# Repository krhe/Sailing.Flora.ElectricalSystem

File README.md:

# Sailing.Flora.ElectricalSystem
Electrical Diagram for Flora

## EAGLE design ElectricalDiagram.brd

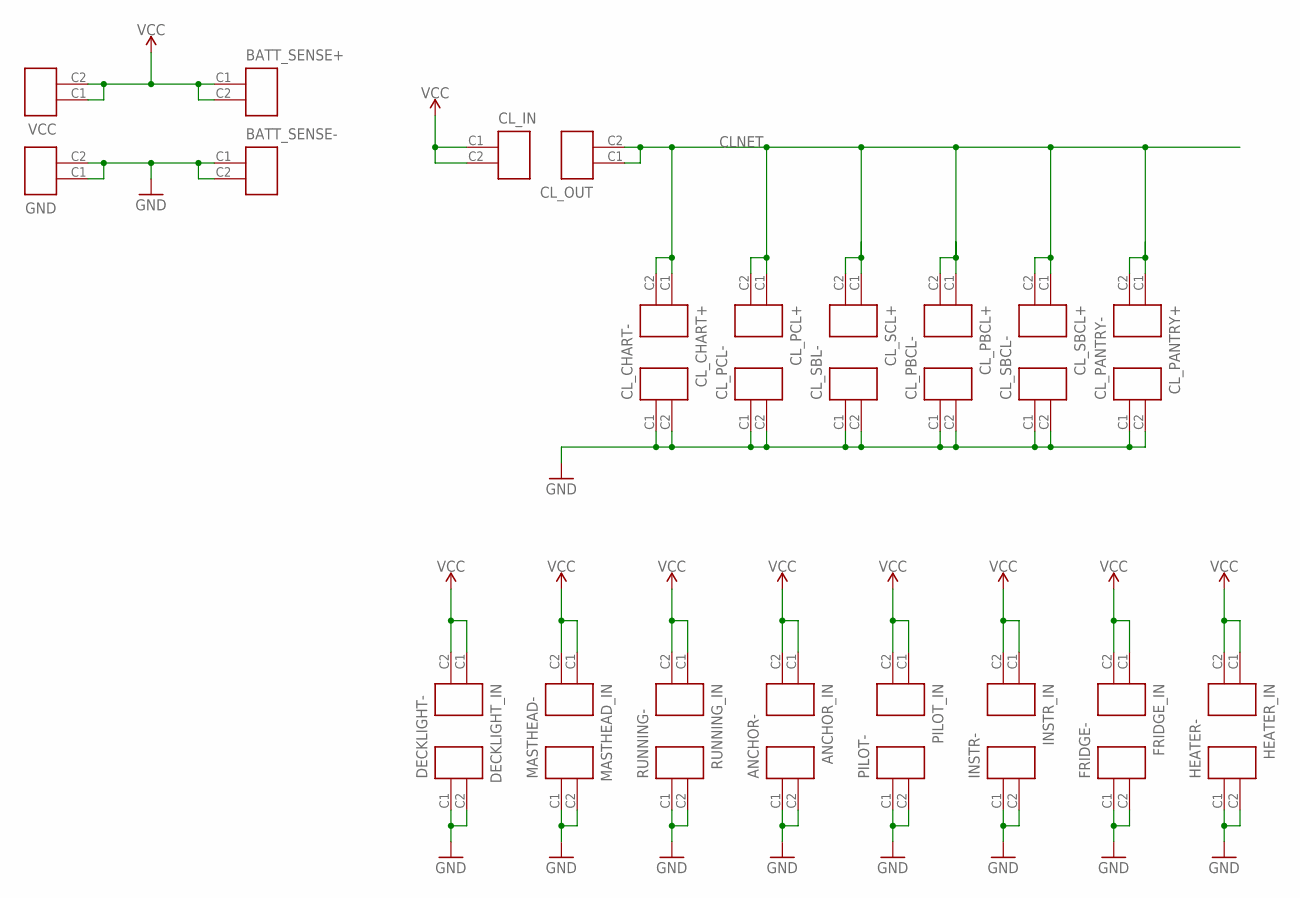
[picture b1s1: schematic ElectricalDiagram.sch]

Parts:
ANCHOR-: 1201-01-001-SPADE
ANCHOR_IN: 1201-01-001-SPADE
BATT_SENSE+: 1201-01-001-SPADE
BATT_SENSE-: 1201-01-001-SPADE
CL_CHART+: 1201-01-001-SPADE
CL_CHART-: 1201-01-001-SPADE
CL_IN: 1201-01-001-SPADE
CL_OUT: 1201-01-001-SPADE
CL_PANTRY+: 1201-01-001-SPADE
CL_PANTRY-: 1201-01-001-SPADE
CL_PBCL+: 1201-01-001-SPADE
CL_PBCL-: 1201-01-001-SPADE
CL_PCL+: 1201-01-001-SPADE
CL_PCL-: 1201-01-001-SPADE
CL_SBCL+: 1201-01-001-SPADE
CL_SBCL-: 1201-01-001-SPADE
CL_SBL-: 1201-01-001-SPADE
CL_SCL+: 1201-01-001-SPADE
DECKLIGHT-: 1201-01-001-SPADE
DECKLIGHT_IN: 1201-01-001-SPADE
FRIDGE-: 1201-01-001-SPADE
FRIDGE_IN: 1201-01-001-SPADE
GND: 1201-01-001-SPADE
HEATER-: 1201-01-001-SPADE
HEATER_IN: 1201-01-001-SPADE
INSTR-: 1201-01-001-SPADE
INSTR_IN: 1201-01-001-SPADE
MASTHEAD-: 1201-01-001-SPADE
MASTHEAD_IN: 1201-01-001-SPADE
PILOT-: 1201-01-001-SPADE
PILOT_IN: 1201-01-001-SPADE
RUNNING-: 1201-01-001-SPADE
RUNNING_IN: 1201-01-001-SPADE
VCC: 1201-01-001-SPADE

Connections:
CLNET: CL_CHART+.C1, CL_CHART+.C2, CL_OUT.C1, CL_OUT.C2, CL_PANTRY+.C1, CL_PANTRY+.C2, CL_PBCL+.C1, CL_PBCL+.C2, CL_PCL+.C1, CL_PCL+.C2, CL_SBCL+.C1, CL_SBCL+.C2, CL_SCL+.C1, CL_SCL+.C2
GND: ANCHOR-.C1, ANCHOR-.C2, BATT_SENSE-.C1, BATT_SENSE-.C2, CL_CHART-.C1, CL_CHART-.C2, CL_PANTRY-.C1, CL_PANTRY-.C2, CL_PBCL-.C1, CL_PBCL-.C2, CL_PCL-.C1, CL_PCL-.C2, CL_SBCL-.C1, CL_SBCL-.C2, CL_SBL-.C1, CL_SBL-.C2, DECKLIGHT-.C1, DECKLIGHT-.C2, FRIDGE-.C1, FRIDGE-.C2, GND.C1, GND.C2, HEATER-.C1, HEATER-.C2, INSTR-.C1, INSTR-.C2, MASTHEAD-.C1, MASTHEAD-.C2, PILOT-.C1, PILOT-.C2, RUNNING-.C1, RUNNING-.C2
VCC: ANCHOR_IN.C1, ANCHOR_IN.C2, BATT_SENSE+.C1, BATT_SENSE+.C2, CL_IN.C1, CL_IN.C2, DECKLIGHT_IN.C1, DECKLIGHT_IN.C2, FRIDGE_IN.C1, FRIDGE_IN.C2, HEATER_IN.C1, HEATER_IN.C2, INSTR_IN.C1, INSTR_IN.C2, MASTHEAD_IN.C1, MASTHEAD_IN.C2, PILOT_IN.C1, PILOT_IN.C2, RUNNING_IN.C1, RUNNING_IN.C2, VCC.C1, VCC.C2

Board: 2 copper layers, 34 parts (0 on the bottom side), 3 nets, no tracks yet.

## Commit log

2020-05-27 Updated board to Flora
